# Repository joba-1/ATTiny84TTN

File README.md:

# ATTiny84TTN
ATTiny84 TTN Node from Leo Korbee (https://www.iot-lab.org/blog/101/) 
+ optional LED, Serial or Pressure by me (JoBa-1)

## Overview

Send data to TheThingsNetwork. For details look at Leo's great site, in general you need to

* Build breadboard node following Leos cirquit diagram (or use his PCB)
    * ATTiny84 (DIP14 format)
    * RFM95W (solder on an ESP32 breakout board where you removed the 2 10K resistors, not the 0k resistor)
    * BME280 breakout board with 6 pins (4 pins is I2C only, we want SPI)
    * Somewhat optional: 100nF and 470µF condensators at the ATTiny +/Gnd pins
    * You dont need the GPIO outputs from Leos cirquit diagram. They are just nice to have on a PCB
    * Optionally connect a led with 470 Ohm resistor from ground to io pin 1 (PB1).
        * Blinks once at startup (50ms)
        * Blinks fast during startup if BME280 is not found (200ms interval)
        * Blinks short on wakeups (8 s interval)
        * Blinks long on aquiring sensor data and sending to TTN (5 min interval)
    * Optionally connect Gnd and pin 3 (PA7) to an USB2Serial Gnd and Rx to monitor at 9600 baud
        * You cant have serial and lora at the same time though. Not enough flash space :(
* Register a TTN account for free
* Login to TTN
* Go to your account menu (upper left) and select Console
* Create an application: Give it a unique name (ID) and a description. Leave the rest at defaults
* Register your node as a device implementing the application
    * Give it a name and description
    * Select activation method ABP (or adapt the code for OTAA, can be changed later in the TTN device settings)
    * Leave rest at defaults
    * Change device settings: Disable frame checks (since the device resets framecounter on restart)
* Copy file src/secconfig_example.h to src/secconfig.h 
* Copy ID and keys from the device page into the new file (use C-Style)
* Connect the ATTiny84 to your UsbAsp programmer, as usual (or use your own flash method, adapting platformio.ini)
    * you can do these connections on the breadboard, but make sure the programmer only uses 3.3V or your BME280 will not be happy
    * Gnd  <-> Gnd
    * MISO <-> MISO
    * MOSI <-> MOSI
    * SCLK <-> SCLK
    * Reset <-> Reset
    *  +   <-> + (if not powered already)
* Connect the programmer to an USB port
* Call pio run --target upload (or click the right buttons in your IDE of choice...)
* Put the ATTiny in your breadboard, connect power and wait for 8s for the first data to arrive at the TTN device page
    * ...if a gateway is in range
    * ...and you did no mistake - it works for me :P
    
Good Luck
    
## Options

Define your payload format on the TTN application page to use more common units. I use this:

### Decoder
```
function Decoder(bytes, port) {
  var decoded = {};
  
  if (port === 1) {
    decoded.mvcc = bytes[0] | bytes[1] << 8;
    decoded.temp = bytes[2] | bytes[3] << 8 | bytes[4] << 16 | bytes[5] << 24;
    decoded.humi = bytes[6] | bytes[7] << 8 | bytes[8] << 16 | bytes[9] << 24;
    decoded.pres = bytes[10]| bytes[11]<< 8 | bytes[12]<< 16 | bytes[13]<< 24;
  }
  else {
    decoded.humi = -1;
  }

  return decoded;
}
```
### Converter
```
function Converter(decoded, port) {
  var converted = {};

  if (port === 1) {
    converted.vcc_V        = decoded.mvcc / 1000;
    converted.temp_degC    = decoded.temp /  100;
    converted.humi_Percent = decoded.humi / 1000;
    converted.pres_hPa     = decoded.pres /  100;
    if (decoded.humi >= 0 && decoded.humi <= 100000) {
      converted.valid = true;
    }
    else {
      converted.valid = false;
    }
  }

  return converted;
}
```
### Validator
```
function Validator(converted, port) {
  if (port === 1) {
    return converted.valid;
  }
  
  return true;
}
```

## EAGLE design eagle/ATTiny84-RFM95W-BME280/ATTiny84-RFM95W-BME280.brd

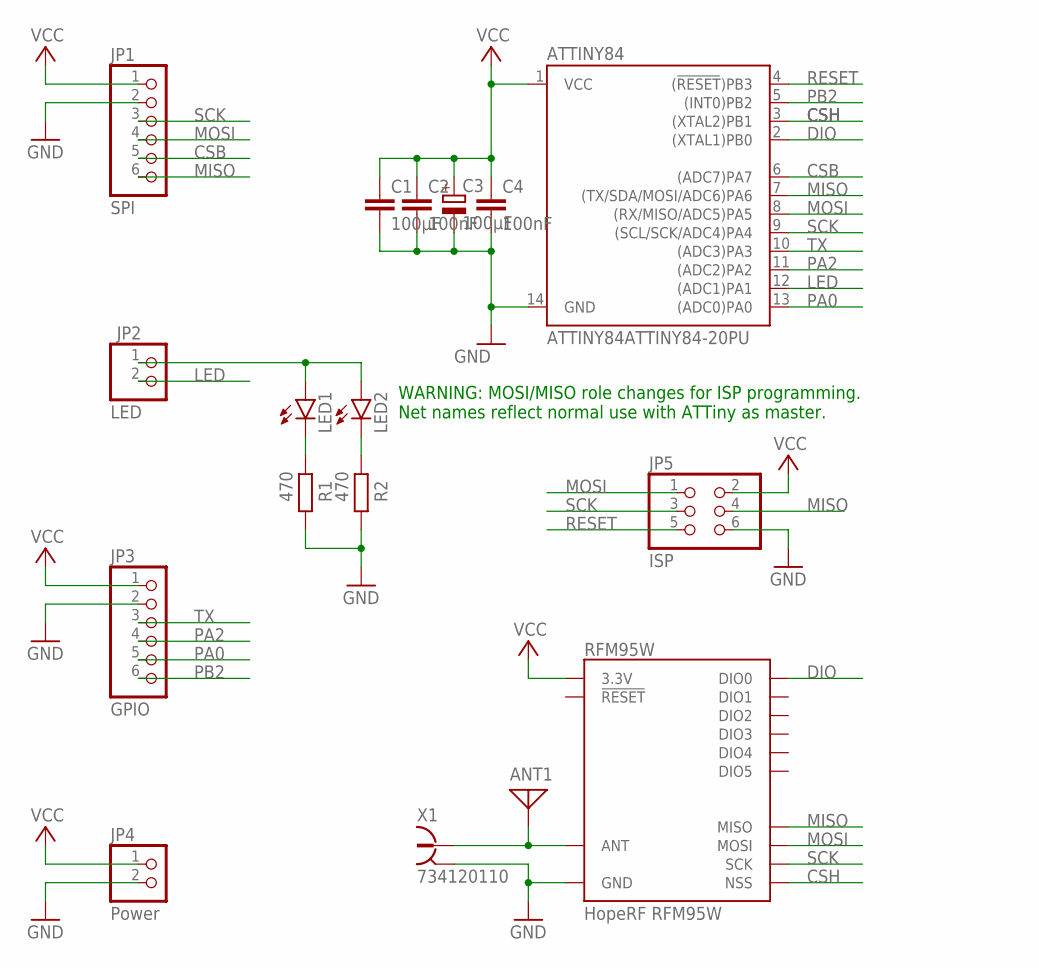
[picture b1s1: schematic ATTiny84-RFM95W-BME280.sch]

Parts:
ANT1: ANTENNA; PAD-01
ATTINY84: ATTINY84ATTINY84-20PU; DIP14
C1: 100µF; C0805
C2: 100nF; C0805
C3: 100µF; E2,5-6
C4: 100nF; C050-050X075
JP1: SPI; 1X06
JP2: LED; 1X02
JP3: GPIO; 1X06
JP4: Power; 1X02
JP5: ISP; 2X03
LED1: LEDCHIP-LED0805; CHIP-LED0805
LED2: LED3MM
R1: 470; R0805
R2: 470; 0207/12
RFM95W: RFM95W; RFM95/96/97/98W
X1: 734120110

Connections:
CSB: ATTINY84.6 ((ADC7)PA7), JP1.5
CSH: ATTINY84.3 ((XTAL2)PB1), RFM95W.NSS
DIO: ATTINY84.2 ((XTAL1)PB0), RFM95W.DIO0
GND: ATTINY84.14 (GND), C1.2, C2.2, C3.-, C4.2, JP1.2, JP3.2, JP4.2, JP5.6, R1.1, R2.1, RFM95W.GND@1 (GND), RFM95W.GND@2 (GND), RFM95W.GND@3 (GND), X1.S@1 (2), X1.S@2 (2), X1.S@3 (2)
LED: ATTINY84.12 ((ADC1)PA1), JP2.2
MISO: ATTINY84.7 ((TX/SDA/MOSI/ADC6)PA6), JP1.6, JP5.4, RFM95W.MISO
MOSI: ATTINY84.8 ((RX/MISO/ADC5)PA5), JP1.4, JP5.1, RFM95W.MOSI
unnamed: ANT1.1, RFM95W.ANT, X1.1
unnamed: LED1.C, R1.2
unnamed: LED2.K (C), R2.2
unnamed: JP2.1, LED1.A, LED2.A
PA0: ATTINY84.13 ((ADC0)PA0), JP3.5
PA2: ATTINY84.11 ((ADC2)PA2), JP3.4
PB2: ATTINY84.5 ((INT0)PB2), JP3.6
RESET: ATTINY84.4 ((!RESET!)PB3), JP5.5
SCK: ATTINY84.9 ((SCL/SCK/ADC4)PA4), JP1.3, JP5.3, RFM95W.SCK
TX: ATTINY84.10 ((ADC3)PA3), JP3.3
VCC: ATTINY84.1 (VCC), C1.1, C2.1, C3.+, C4.1, JP1.1, JP3.1, JP4.1, JP5.2, RFM95W.3.3V

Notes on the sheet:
WARNING: MOSI/MISO role changes for ISP programming. Net names reflect normal use with ATTiny as master.

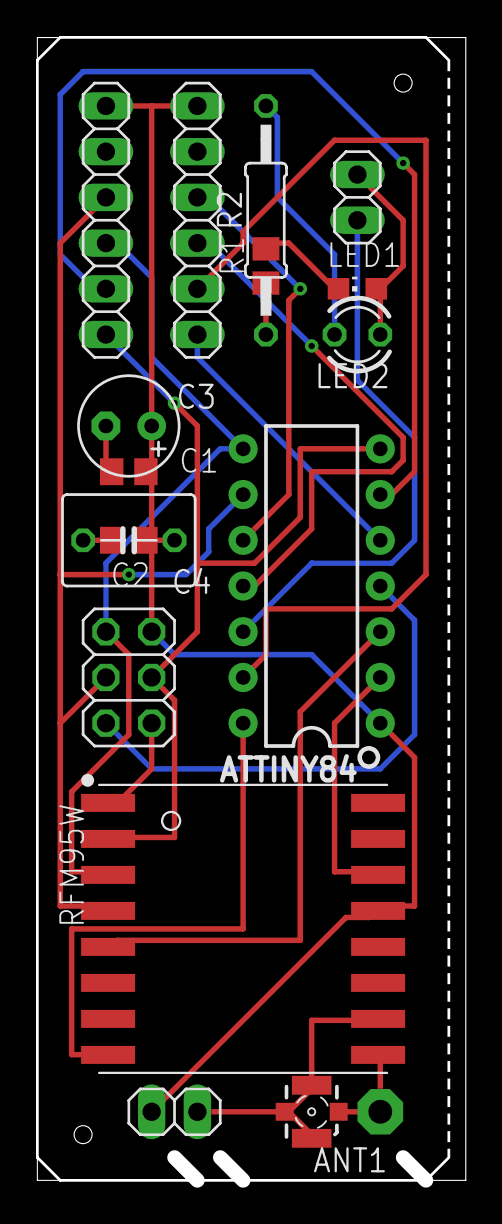
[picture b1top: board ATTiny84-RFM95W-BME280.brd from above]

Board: 2 copper layers, 23.1 x 63.2 mm, 17 parts (0 on the bottom side), 18 nets.

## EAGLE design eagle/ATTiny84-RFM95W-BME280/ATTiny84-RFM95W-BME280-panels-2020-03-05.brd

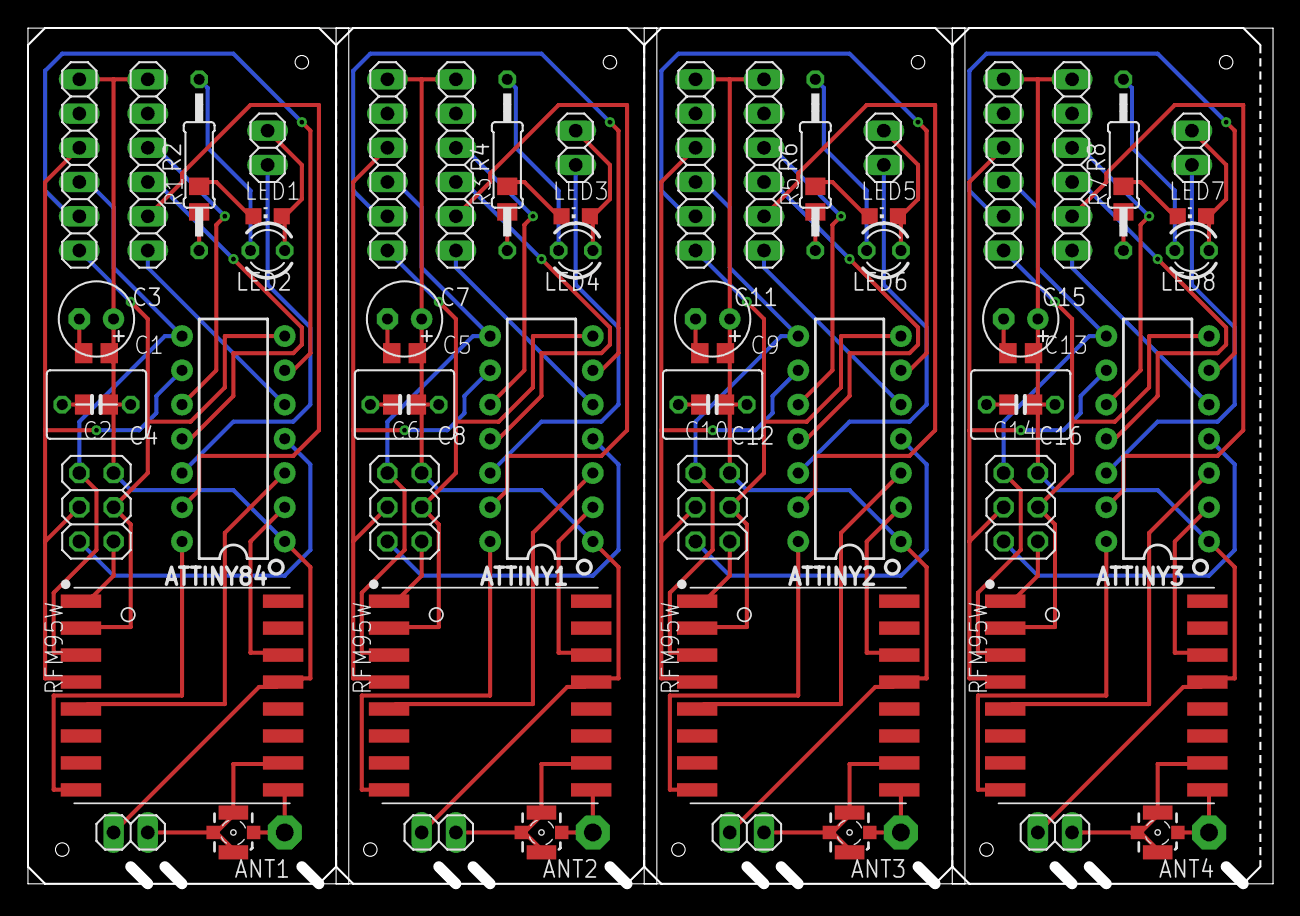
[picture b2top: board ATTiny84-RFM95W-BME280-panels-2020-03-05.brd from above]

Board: 2 copper layers, 91.6 x 63.2 mm, 68 parts (0 on the bottom side), 72 nets.

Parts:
ANT1, ANT2, ANT3, ANT4: PAD-01
ATTINY1, ATTINY2, ATTINY3, ATTINY84: ATTINY84ATTINY84-20PU; DIP14
C1, C5, C9, C13: 100µF; C0805
C2, C6, C10, C14: 100nF; C0805
C3, C7, C11, C15: 100µF; E2,5-6
C4, C8, C12, C16: 100nF; C050-050X075
JP1, JP6, JP11, JP16: SPI; 1X06
JP2, JP7, JP12, JP17: LED; 1X02
JP3, JP8, JP13, JP18: GPIO; 1X06
JP4, JP9, JP14, JP19: Power; 1X02
JP5, JP10, JP15, JP20: ISP; 2X03
LED1, LED3, LED5, LED7: CHIP-LED0805
LED2, LED4, LED6, LED8: LED3MM
R1, R3, R5, R7: 470; R0805
R2, R4, R6, R8: 470; 0207/12
RFM95W, RFM95W1, RFM95W2, RFM95W3: RFM95W; RFM95/96/97/98W
X1, X2, X3, X4: 734120110

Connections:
CSB: ATTINY84.6, JP1.5
CSB1: ATTINY1.6, JP6.5
CSB2: ATTINY2.6, JP11.5
CSB3: ATTINY3.6, JP16.5
CSH: ATTINY84.3, RFM95W.NSS
CSH1: ATTINY1.3, RFM95W1.NSS
CSH2: ATTINY2.3, RFM95W2.NSS
CSH3: ATTINY3.3, RFM95W3.NSS
DIO: ATTINY84.2, RFM95W.DIO0
DIO1: ATTINY1.2, RFM95W1.DIO0
DIO2: ATTINY2.2, RFM95W2.DIO0
DIO3: ATTINY3.2, RFM95W3.DIO0
GND: ATTINY84.14, C1.2, C2.2, C3.-, C4.2, JP1.2, JP3.2, JP4.2, JP5.6, R1.1, R2.1, RFM95W.GND@1, RFM95W.GND@2, RFM95W.GND@3, X1.S@1, X1.S@2, X1.S@3
GND1: ATTINY1.14, C5.2, C6.2, C7.-, C8.2, JP6.2, JP8.2, JP9.2, JP10.6, R3.1, R4.1, RFM95W1.GND@1, RFM95W1.GND@2, RFM95W1.GND@3, X2.S@1, X2.S@2, X2.S@3
GND2: ATTINY2.14, C9.2, C10.2, C11.-, C12.2, JP11.2, JP13.2, JP14.2, JP15.6, R5.1, R6.1, RFM95W2.GND@1, RFM95W2.GND@2, RFM95W2.GND@3, X3.S@1, X3.S@2, X3.S@3
GND3: ATTINY3.14, C13.2, C14.2, C15.-, C16.2, JP16.2, JP18.2, JP19.2, JP20.6, R7.1, R8.1, RFM95W3.GND@1, RFM95W3.GND@2, RFM95W3.GND@3, X4.S@1, X4.S@2, X4.S@3
LED: ATTINY84.12, JP2.2
LED1: ATTINY1.12, JP7.2
LED2: ATTINY2.12, JP12.2
LED3: ATTINY3.12, JP17.2
MISO: ATTINY84.7, JP1.6, JP5.4, RFM95W.MISO
MISO1: ATTINY1.7, JP6.6, JP10.4, RFM95W1.MISO
MISO2: ATTINY2.7, JP11.6, JP15.4, RFM95W2.MISO
MISO3: ATTINY3.7, JP16.6, JP20.4, RFM95W3.MISO
MOSI: ATTINY84.8, JP1.4, JP5.1, RFM95W.MOSI
MOSI1: ATTINY1.8, JP6.4, JP10.1, RFM95W1.MOSI
MOSI2: ATTINY2.8, JP11.4, JP15.1, RFM95W2.MOSI
MOSI3: ATTINY3.8, JP16.4, JP20.1, RFM95W3.MOSI
unnamed: ANT1.1, RFM95W.ANT, X1.1
unnamed: ANT2.1, RFM95W1.ANT, X2.1
unnamed: LED1.C, R1.2
unnamed: LED2.K, R2.2
unnamed: LED3.C, R3.2
unnamed: LED4.K, R4.2
unnamed: JP2.1, LED1.A, LED2.A
unnamed: JP7.1, LED3.A, LED4.A
unnamed: ANT3.1, RFM95W2.ANT, X3.1
unnamed: LED5.C, R5.2
unnamed: LED6.K, R6.2
unnamed: JP12.1, LED5.A, LED6.A
unnamed: ANT4.1, RFM95W3.ANT, X4.1
unnamed: LED7.C, R7.2
unnamed: LED8.K, R8.2
unnamed: JP17.1, LED7.A, LED8.A
PA0: ATTINY84.13, JP3.5
PA1: ATTINY1.11, JP8.4
PA2: ATTINY84.11, JP3.4
PA3: ATTINY1.13, JP8.5
PA4: ATTINY2.11, JP13.4
PA5: ATTINY2.13, JP13.5
PA6: ATTINY3.11, JP18.4
PA7: ATTINY3.13, JP18.5
PB1: ATTINY1.5, JP8.6
PB2: ATTINY84.5, JP3.6
PB3: ATTINY2.5, JP13.6
PB4: ATTINY3.5, JP18.6
RESET: ATTINY84.4, JP5.5
RESET1: ATTINY1.4, JP10.5
RESET2: ATTINY2.4, JP15.5
RESET3: ATTINY3.4, JP20.5
SCK: ATTINY84.9, JP1.3, JP5.3, RFM95W.SCK
SCK1: ATTINY1.9, JP6.3, JP10.3, RFM95W1.SCK
SCK2: ATTINY2.9, JP11.3, JP15.3, RFM95W2.SCK
SCK3: ATTINY3.9, JP16.3, JP20.3, RFM95W3.SCK
TX: ATTINY84.10, JP3.3
TX1: ATTINY1.10, JP8.3
TX2: ATTINY2.10, JP13.3
TX3: ATTINY3.10, JP18.3
VCC: ATTINY84.1, C1.1, C2.1, C3.+, C4.1, JP1.1, JP3.1, JP4.1, JP5.2, RFM95W.3.3V
VCC1: ATTINY1.1, C5.1, C6.1, C7.+, C8.1, JP6.1, JP8.1, JP9.1, JP10.2, RFM95W1.3.3V
VCC2: ATTINY2.1, C9.1, C10.1, C11.+, C12.1, JP11.1, JP13.1, JP14.1, JP15.2, RFM95W2.3.3V
VCC3: ATTINY3.1, C13.1, C14.1, C15.+, C16.1, JP16.1, JP18.1, JP19.1, JP20.2, RFM95W3.3.3V

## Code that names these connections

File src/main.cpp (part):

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
/*
  Hardware setup
  Attiny84 using the Arduino pin numbers! PB0 = 0 etc.


  Atmel ATtiny84A PU
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  Connections:
  RFM95W   ATtiny84

  DIO0 -- PB0
  MISO -- MOSI
  MOSI -- MISO
  SCK  -- SCK
  NSS  -- PB1 (this is Chipselect)

  Bosch BME280 sensor used with tinySPI....
  BME280  ATtiny84
  SCL -- SCK
  SDA -- MISO
  SDO -- MOSI
  CSB -- PA7 (this is Chipselect)(Arduino pin 7)
*/

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
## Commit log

2019-12-10 add serial out and led indicator for debug
2019-12-10 use float for uint64_t to save flash for pressure (not enough...)
2019-12-11 preliminary elimination of float
2019-12-12 bme now with pressure, no lora but debug output
2019-12-13 make room in ram/flash for sending pressure too
2019-12-13 add decoder to readme and some minor cosmetics
2019-12-20 describe Apache/InfluxDB/Grafana integration
2020-03-04 final version with pressure
2020-03-04 add BME280 driver from Bosch
2020-03-04 bme280 lib in 32bit mode and no nullptr checks
2020-03-04 save flash and enable led and lora
2020-03-05 add eagle schematics, board and pcb zip

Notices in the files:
src/main.cpp:
@license Attribution-NonCommercial-ShareAlike 4.0 International (CC BY-NC-SA 4.0)
parts and their libraries:
SparkFun-IC-Microcontroller: Licensing: Creative Commons ShareAlike 4.0 International - https://creativecommons.org/licenses/by-sa/4.0
